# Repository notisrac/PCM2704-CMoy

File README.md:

# PCM2704-CMoy
[CMoy](https://tangentsoft.net/audio/cmoy/) headphone amp with a [PCM2704](http://www.ti.com/product/PCM2704) DAC

# Technical highlights
* Charge-pump power supply (instead of rail splitter)
* Runs off a 18V wallwart power supply
* The DAC is self powered

## Acknowledgements
[http://www.pavouk.org/hw/usbdacpcm2704/en_index.html](http://www.pavouk.org/hw/usbdacpcm2704/en_index.html)
[http://www.isendev.com/app/entry/12](http://www.isendev.com/app/entry/12)

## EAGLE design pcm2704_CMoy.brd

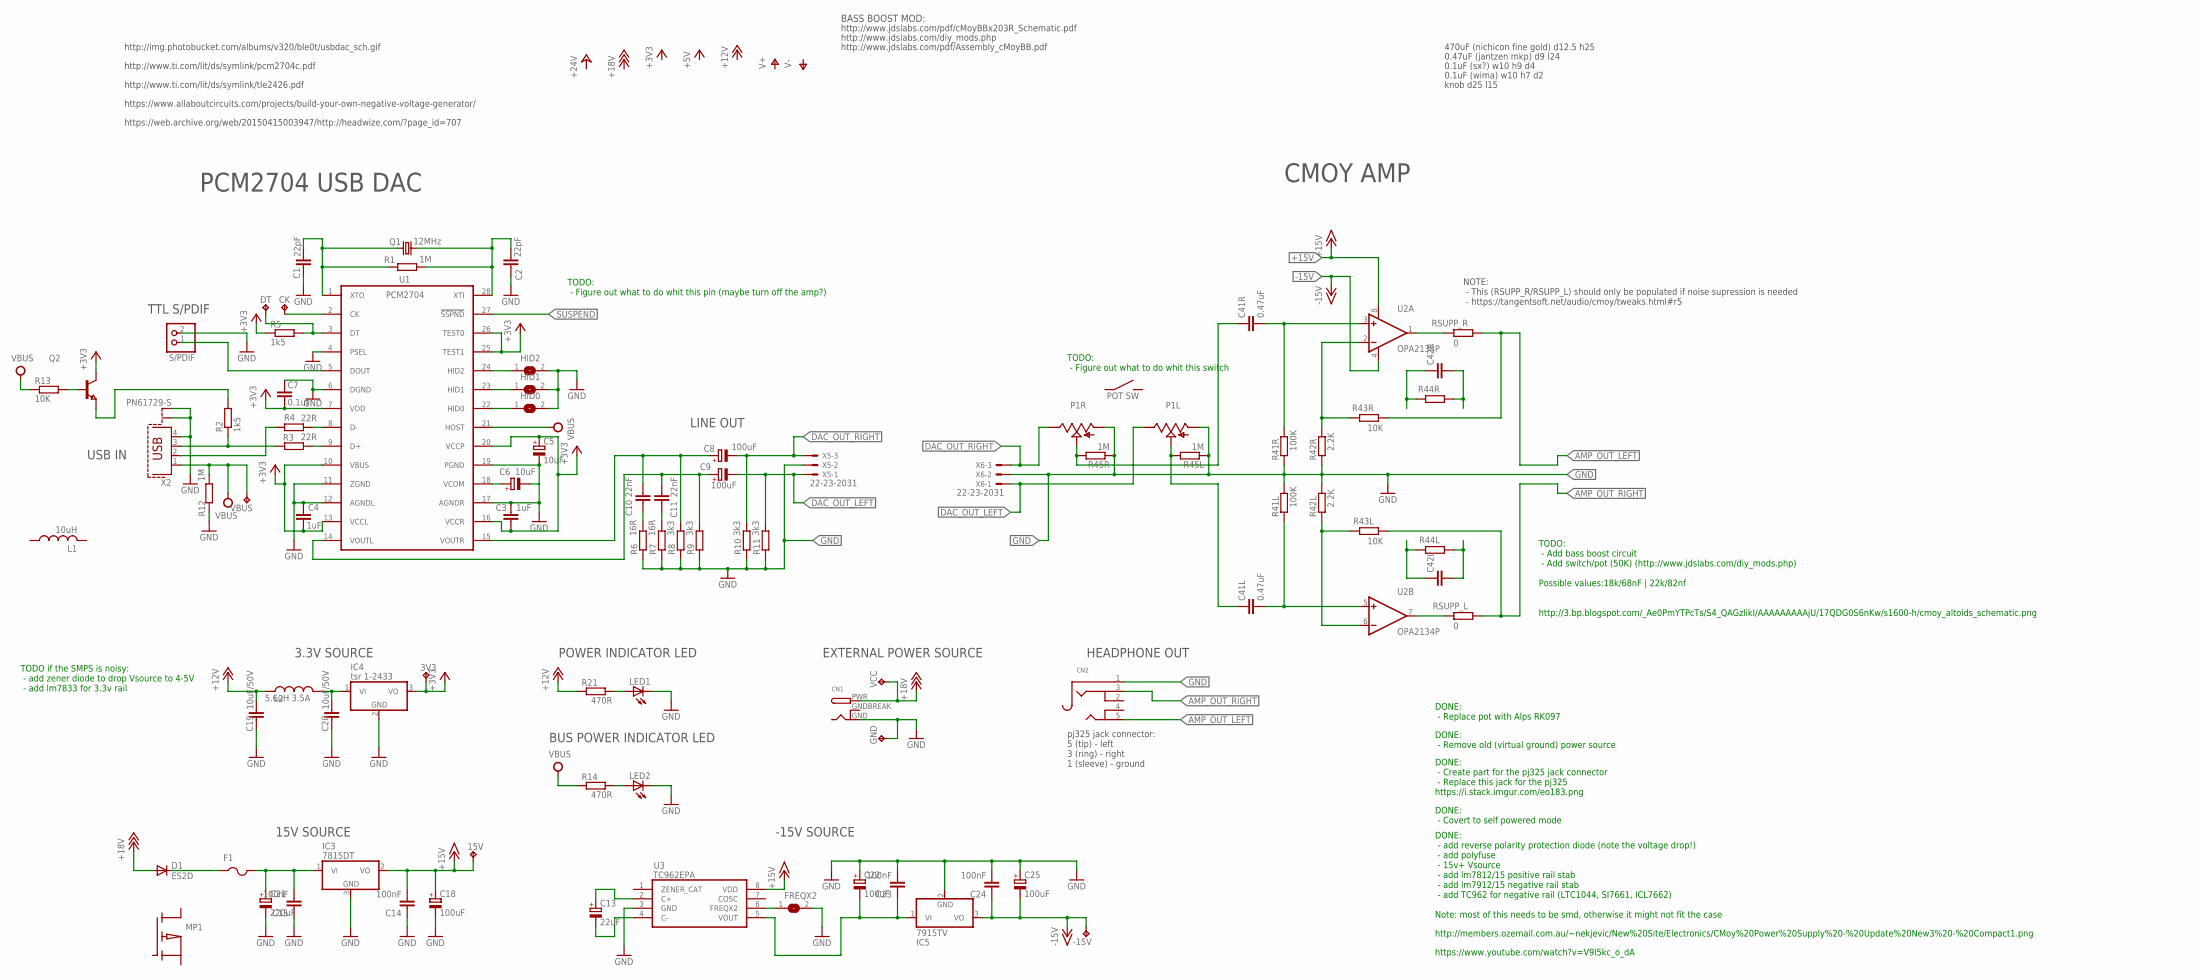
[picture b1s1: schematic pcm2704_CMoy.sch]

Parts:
3V3, 15V: TPTP20R; TP20R
-15V: TPTP20R; TP20R
C1, C2: 22pF; C0805
C3, C4: 1uF; C0805
C5, C6: 10uF; E2,5-7
C7: 0.1uF; C0805
C8, C9: 100uF; E3,5-10
C10, C11: 22nF; C050-025X075
C13: 22uF; E2,5-7
C14, C15, C23, C24: 100nF; C1206
C18, C22, C25: 100uF; E2,5-7
C19, C20: 10uF/50V; C1206
C21: 220uF; E2,5-7
C41L, C41R: 0.47uF; C27.5B11
C42L, C42R: C7.5/4; C7.5B4
CK: TPTP20R; TP20R
CN1: DCBARRELPTH; DCJACK_2MM_PTH
CN2: AUDIO_3.5MMJACKPTH; 4UCONN_05550
D1: ES2D; SMB
DT: TPTP20R; TP20R
F1: PTCFUSE-1812; 1812
FREQX2: SJ
GND: TPTP20R; TP20R
HID0, HID1, HID2: SJ
IC3: 7815DT; TO252
IC4: tsr 1-2433; TO220V
IC5: 7915TV; TO220V
L1: 10uH; L1812
L2: 5.6uH 3.5A; L1812
LED1, LED2: LED3MM
MP1: PMOS; SOT23
P1: ALPS_RK0971221Z0N; ALPS_RK0971221Z0X
Q1: 12MHz; HC49/S
Q2: NPN-TRANSISTOR_SOT23; SOT23
R1, R12: 1M; M0805
R2, R5: 1k5; R0805
R3, R4: 22R; R0805
R6, R7: 16R; 0204/7
R8, R9, R10, R11: 3k3; 0204/7
R13: 10K; R0805
R14, R21: 470R; 0204/7
R41L, R41R: 100K; 0204/7
R42L, R42R: 2.2K; 0204/7
R43L, R43R: 10K; 0204/7
R44L, R44R: R-EU_0204/7; 0204/7
R45L, R45R: 1M; 0204/7
RSUPP_L: 0; 0204/7
RSUPP_R: 0; 0204/7
S/PDIF: PINHD-1X2; 1X02
U1: PCM2704; SSOP28DB
U2: OPA2134P; DIL08
U3: TC962EPA; PDIP8_300MC
VBUS: TPTP20R; TP20R
VCC: TPTP20R; TP20R
X2: PN61729-S
X5, X6: 22-23-2031

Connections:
+3V3: 3V3.TP, C3.1, C4.2, C5.+, C7.2, IC4.3 (VO), Q2.3 (C), R5.1, U1.7 (VDD), U1.10 (VBUS), U1.13 (VCCL), U1.16 (VCCR), U1.20 (VCCP), U1.25 (TEST1), U1.26 (TEST0)
+12V: C19.2, L2.1, R21.1
+15V: 15V.TP, C14.2, C18.+, IC3.2 (VO), U2.8 (V+), U3.8 (VDD)
+18V: CN1.PWR, D1.A, VCC.TP
-15V: -15V.TP, C24.1, C25.-, IC5.3 (VO), U2.4 (V-)
AMP_OUT_LEFT: CN2.5, R43R.1, RSUPP_R.1
AMP_OUT_RIGHT: CN2.3, R43L.1, RSUPP_L.1
DAC_OUT_LEFT: C9.-, P1.I1 (3), R11.2, X5.1, X6.1
DAC_OUT_RIGHT: C8.-, P1.I2 (3), R10.2, X5.3, X6.3
GND: C1.2, C2.2, C3.2, C4.1, C5.-, C6.-, C7.1, C14.1, C15.1, C18.-, C19.1, C20.1, C21.-, C22.+, C23.2, C24.2, C25.+, CN1.GND, CN2.1, FREQX2.2, GND.TP, HID0.2, HID1.2, HID2.2, IC3.3 (GND), IC4.2 (GND), IC5.2 (GND), LED1.K (C), LED2.K (C), P1.G1 (1), P1.G2 (1), R6.1, R7.1, R8.1, R9.1, R10.1, R11.1, R12.1, R41L.2, R41R.1, R42L.2, R42R.1, R45L.1, R45R.1, S/PDIF.2, U1.4 (PSEL), U1.6 (DGND), U1.11 (ZGND), U1.12 (AGNDL), U1.17 (AGNDR), U1.19 (PGND), U3.3 (GND), X2.4, X2.S1, X2.S2, X5.2, X6.2
GNDBREAK: CN1.GNDBREAK
unnamed: D1.C, F1.1
unnamed: LED2.A, R14.2
unnamed: R4.1, X2.2
unnamed: R4.2, U1.8 (D-)
unnamed: R2.1, R3.1, X2.3
unnamed: R3.2, U1.9 (D+)
unnamed: C20.2, IC4.1 (VI), L2.2
unnamed: LED1.A, R21.2
unnamed: CK.TP, U1.2 (CK)
unnamed: C1.1, Q1.1, R1.1, U1.1 (XTO)
unnamed: C2.1, Q1.2, R1.2, U1.28 (XTI)
unnamed: HID2.1, U1.24 (HID2)
unnamed: C42L.2, R44L.1
unnamed: C42L.1, R44L.2
unnamed: HID1.1, U1.23 (HID1)
unnamed: HID0.1, U1.22 (HID0)
unnamed: C41L.2, R41L.1, U2.5 (+IN)
unnamed: C41R.2, R41R.2, U2.3 (+IN)
unnamed: C41R.1, P1.O2 (2), R45R.2
unnamed: DT.TP, R5.2, U1.3 (DT)
unnamed: C41L.1, P1.O1 (2), R45L.2
unnamed: R42R.2, R43R.2, U2.2 (-IN)
unnamed: R42L.1, R43L.2, U2.6 (-IN)
unnamed: C15.2, C21.+, F1.2, IC3.1 (VI)
unnamed: FREQX2.1, U3.6 (FREQX2)
unnamed: C10.2, R6.2
unnamed: C11.2, R7.2
unnamed: C8.+, C10.1, R8.2, U1.15 (VOUTR)
unnamed: C9.+, C11.1, R9.2, U1.14 (VOUTL)
unnamed: C13.+, U3.2 (C+)
unnamed: C13.-, U3.4 (C-)
unnamed: S/PDIF.1, U1.5 (DOUT)
unnamed: RSUPP_R.2, U2.1 (OUT)
unnamed: C22.-, C23.1, IC5.1 (VI), U3.5 (VOUT)
unnamed: RSUPP_L.2, U2.7 (OUT)
unnamed: C42R.1, R44R.2
unnamed: C42R.2, R44R.1
unnamed: Q2.1 (B), R13.2
unnamed: Q2.2 (E), R2.2
S1: P1.S1
S2: P1.S2
SUSPEND: U1.27 (!SSPND)
VBUS: R12.2, R13.1, R14.1, U1.21 (HOST), VBUS.TP, X2.1
VCOM: C6.+, U1.18 (VCOM)

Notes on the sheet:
LINE OUT
USB IN
PCM2704 USB DAC
TTL S/PDIF
470uF (nichicon fine gold) d12.5 h25
0.47uF (jantzen mkp) d9 l24
0.1uF (sx?) w10 h9 d4
0.1uF (wima) w10 h7 d2
knob d25 l15
http://img.photobucket.com/albums/v320/ble0t/usbdac_sch.gif
http://www.ti.com/lit/ds/symlink/pcm2704c.pdf
3.3V SOURCE
POWER INDICATOR LED
CMOY AMP
EXTERNAL POWER SOURCE
HEADPHONE OUT
http://www.ti.com/lit/ds/symlink/tle2426.pdf
https://www.allaboutcircuits.com/projects/build-your-own-negative-voltage-generator/
http://www.jdslabs.com/pdf/cMoyBBx203R_Schematic.pdf
http://www.jdslabs.com/diy_mods.php
http://www.jdslabs.com/pdf/Assembly_cMoyBB.pdf
BASS BOOST MOD:
http://members.ozemail.com.au/~nekjevic/New%20Site/Electronics/CMoy%20Power%20Supply%20-%20Update%20New3%20-%20Compact1.png
DONE: - add reverse polarity protection diode (note the voltage drop!) - add polyfuse - 15v+ Vsource - add lm7812/15 positive rail stab - add lm7912/15 negative rail stab - add TC962 for negative rail (LTC1044, SI7661, ICL7662) Note: most of this needs to be smd, otherwise it might not fit the case
DONE: - Covert to self powered mode
DONE: - Remove old (virtual ground) power source
DONE: - Replace pot with Alps RK097
TODO: - Add bass boost circuit - Add switch/pot (50K) (http://www.jdslabs.com/diy_mods.php) Possible values:18k/68nF | 22k/82nf http://3.bp.blogspot.com/_Ae0PmYTPcTs/S4_QAGzlikI/AAAAAAAAAjU/17QDG0S6nKw/s1600-h/cmoy_altoids_schematic.png
https://www.youtube.com/watch?v=V9l5kc_o_dA
https://web.archive.org/web/20150415003947/http://headwize.com/?page_id=707
NOTE: - This (RSUPP_R/RSUPP_L) should only be populated if noise supression is needed - https://tangentsoft.net/audio/cmoy/tweaks.html#r5
DONE: - Create part for the pj325 jack connector - Replace this jack for the pj325 https://i.stack.imgur.com/eo183.png
TODO: - Figure out what to do whit this pin (maybe turn off the amp?)
15V SOURCE
-15V SOURCE
TODO: - Figure out what to do whit this switch
pj325 jack connector: 5 (tip) - left 3 (ring) - right 1 (sleeve) - ground
TODO if the SMPS is noisy: - add zener diode to drop Vsource to 4-5V - add lm7833 for 3.3v rail
BUS POWER INDICATOR LED

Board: 2 copper layers, 87 parts (0 on the bottom side), 51 nets, no tracks yet.

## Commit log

2018-01-02 - Replaced current pot with Alps RK097
    - Removed old (virtual ground) power source
    - Added reverse polarity protection diode - still needs work (should it be a mosfet?)
    - Added polyfuse
    - Added +15V rail
    - Added -15V rail (TC962)
2018-01-06 Minor component placement changes
2018-01-06 - Replaced the audio jack with a PF325
    - Renamed the resistors and the capacitors in the amp to reflect the side they are used on (R/L)
2018-01-09 - Modified PCM2704 to be self powered
    - Modified the resistor names of the dac to match the example schematic in the datasheet
2018-01-09 - Added D+ pullup activator transistor
2018-01-10 - Modified capacitor names to match the datasheet example (DAC)
    - Fixed a few capacitor values that did not match the datasheet example (DAC)
2018-01-10 - Removed the external rom connector, because it does not support descriptor overwriting in self powered mode
2018-01-10 - Cosmetics
    - Added bus power indicator led
2018-01-13 - Added resistor between the wiper and ground of the volume pot
    - Fixed the pot direction
2018-07-28 Added GA beacon to the README

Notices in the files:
parts and their libraries:
microbuilder: This work is placed in the public domain, and may be freely used for commercial and non-commercial work with the following conditions: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
